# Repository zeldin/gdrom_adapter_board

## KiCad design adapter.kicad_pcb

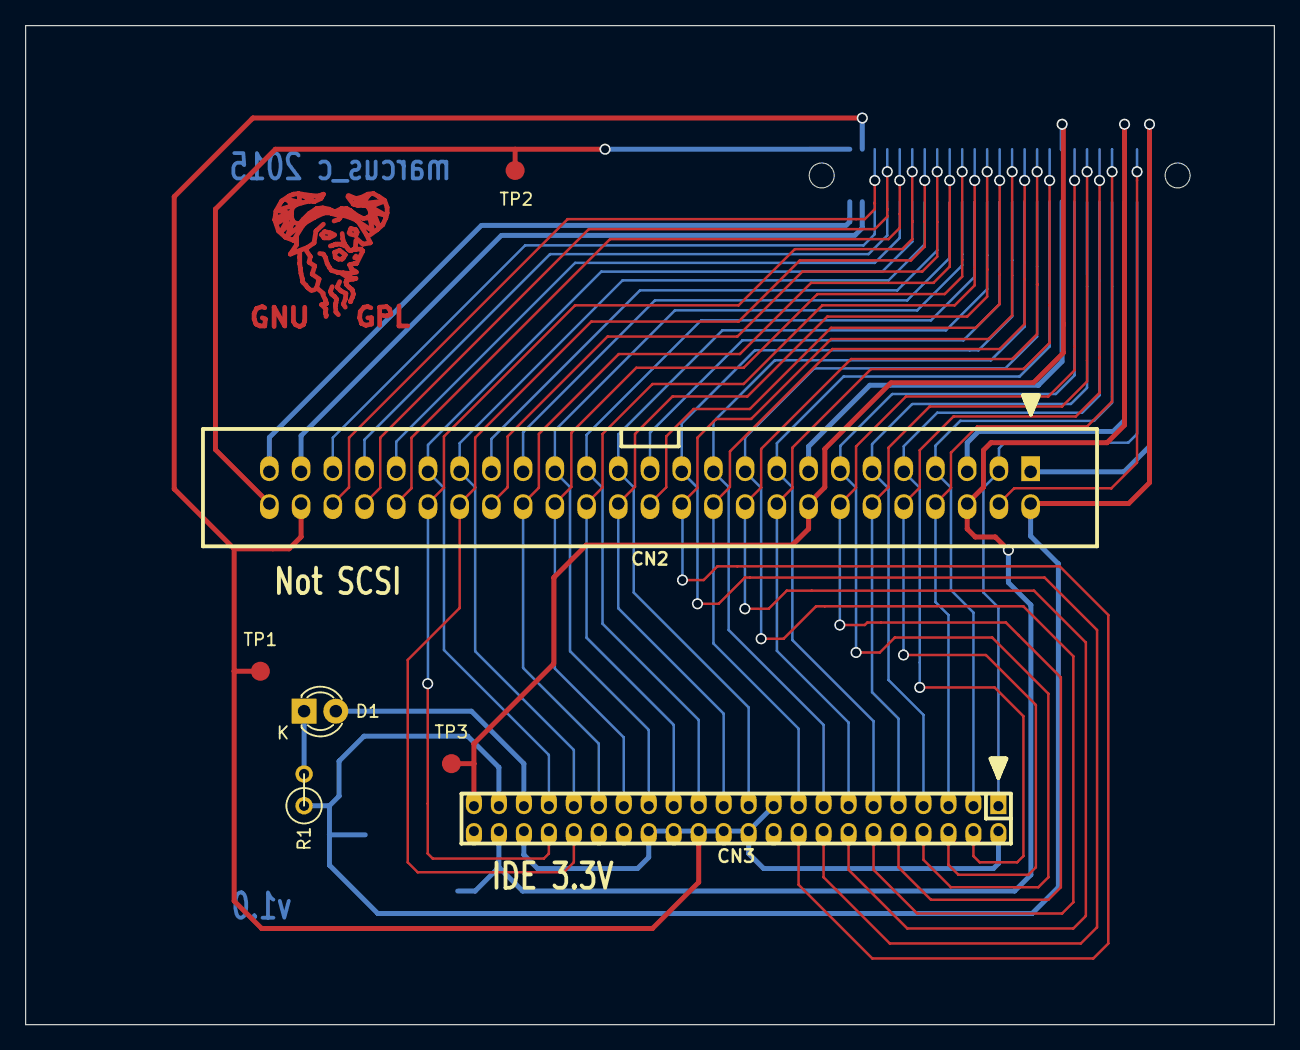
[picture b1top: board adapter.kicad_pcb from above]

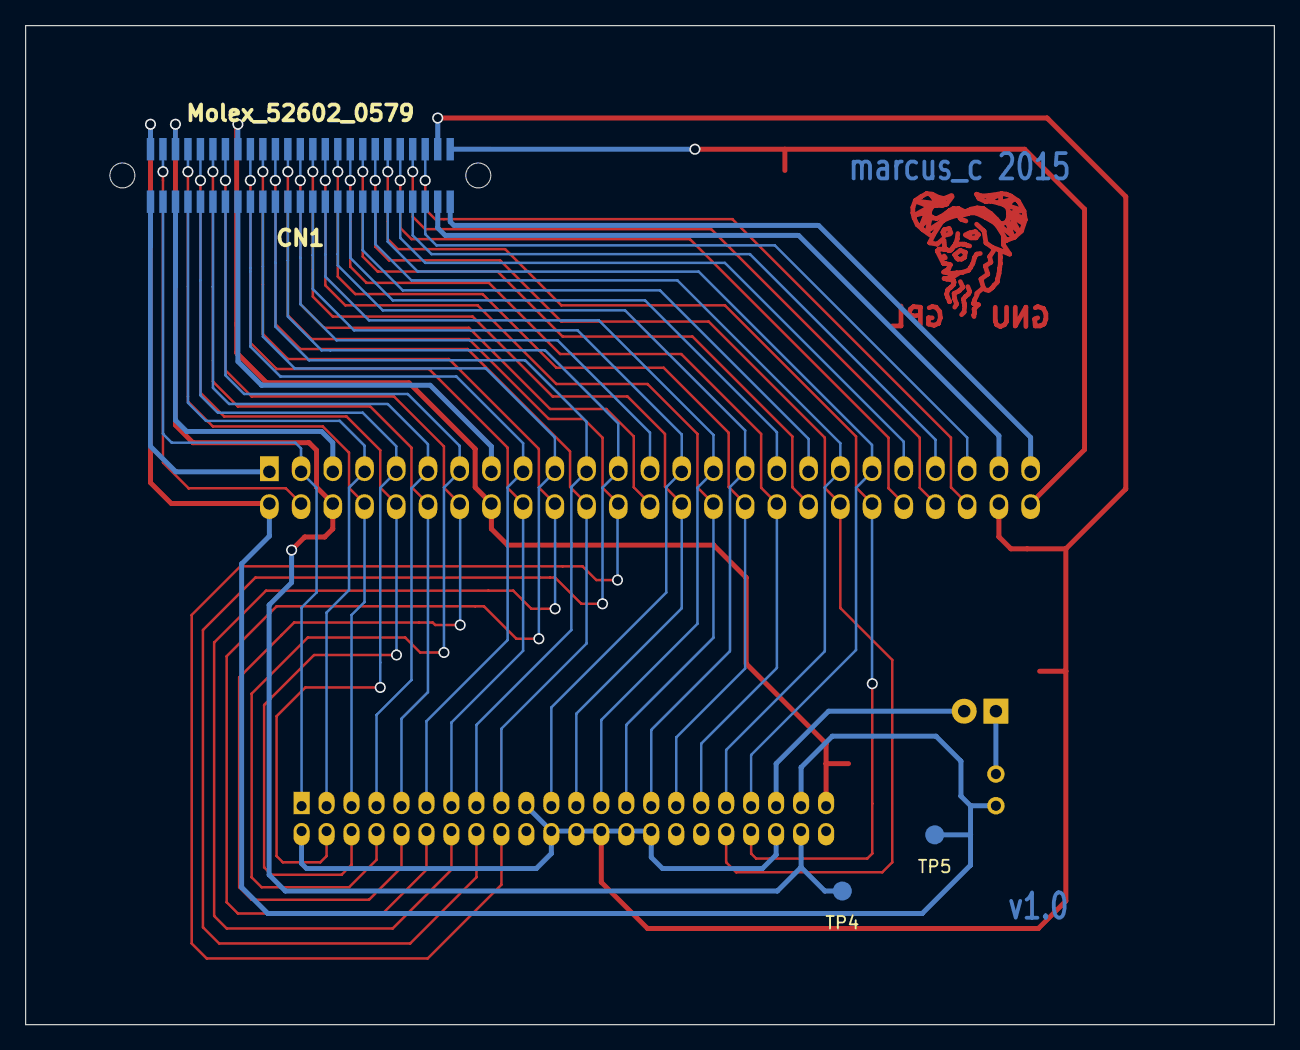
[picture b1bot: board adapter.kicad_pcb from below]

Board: 2 copper layers, 100.0 x 80.0 mm, 10 parts (3 on the bottom side), 52 nets.

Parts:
CN1: Molex_52602_0579
CN2: CONN_25X2; vasch_strip_25x2
CN3: CONN_02X22; pin_strip_2mm_22x2
D1: LED; LED-3MM
R1: 1k; R1
TP1, TP2, TP3, TP4, TP5: Measurement_Point_Round-SMD-Pad_Small

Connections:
+3V3: CN1.B1, CN2.2, CN3.41, R1.1, TP5.1
+3V3_2: CN1.A1, CN2.1
+5V: CN1.B3, CN2.6, CN3.42, TP4.1
+5V_2: CN1.A3, CN2.5
+12V: CN1.B25, CN2.50, TP2.1
+12V_2: CN1.A25, CN2.49
/A0: CN1.A19, CN2.37, CN3.35
/A1: CN1.B17, CN2.34, CN3.33
/A2: CN1.B19, CN2.38, CN3.36
/ACTIVEn: CN3.39, D1.2
/CD_CLK: CN1.B23, CN2.46
/CS0n: CN1.A20, CN2.39, CN3.37
/CS1n: CN1.B20, CN2.40, CN3.38
/D0: CN1.B11, CN2.22, CN3.17
/D1: CN1.A11, CN2.21, CN3.15
/D2: CN1.B9, CN2.18, CN3.13
/D3: CN1.A9, CN2.17, CN3.11
/D4: CN1.B6, CN2.12, CN3.9
/D5: CN1.A6, CN2.11, CN3.7
/D6: CN1.B4, CN2.8, CN3.5
/D7: CN1.A4, CN2.7, CN3.3
/D8: CN1.A5, CN2.9, CN3.4
/D9: CN1.B5, CN2.10, CN3.6
/D10: CN1.A7, CN2.13, CN3.8
/D11: CN1.B7, CN2.14, CN3.10
/D12: CN1.A10, CN2.19, CN3.12
/D13: CN1.B10, CN2.20, CN3.14
/D14: CN1.A12, CN2.23, CN3.16
/D15: CN1.B12, CN2.24, CN3.18
/DMACKn: CN1.A16, CN2.31, CN3.29
/DMARQ: CN1.A14, CN2.27, CN3.21
/EMPH: CN1.A17, CN2.33
/G_RST: CN1.A2, CN2.3, CN3.1
/INTRQ: CN1.B16, CN2.32, CN3.31
/IORDY: CN1.B15, CN2.30, CN3.27
/LRCK: CN1.B22, CN2.44
/RDn: CN1.A15, CN2.29, CN3.25
/SCK: CN1.A22, CN2.43
/SDAT: CN1.A23, CN2.45
/WRn: CN1.B14, CN2.28, CN3.23
/xA13: CN1.A13, CN2.25
/xA18: CN1.A18, CN2.35
/xA21: CN1.A21, CN2.41
/xB2: CN1.B2, CN2.4
/xB13: CN1.B13, CN2.26
/xB18: CN1.B18, CN2.36
/xB21: CN1.B21, CN2.42
GND: CN1.B8, CN2.16, CN3.43, TP3.1
GND2: CN1.A8, CN2.15
unnamed: D1.1, R1.2
P.GND: CN1.B24, CN2.48, CN3.2, CN3.19, CN3.22, CN3.24, CN3.26, CN3.28, CN3.30, CN3.40, TP1.1
P.GND_2: CN1.A24, CN2.47

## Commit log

2015-12-05 Generated gerbers
2015-12-05 Add GPL license
2016-01-13 Hide REF for gnu
2016-01-13 Move CN1 footprint closer to PCB edge to improve fan clearance
2016-01-15 Consolidate all power lines connected on the DC mainboard
2016-01-15 New gerbers
2016-01-17 Add PWR_FLAG to prevent ERC errors
